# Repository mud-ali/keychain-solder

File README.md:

# keychain-solder

part of https://solder.hackclub.com/

## Description

This project is just a simple keychain with a few LEDs and a motor that turns on with the press of a button

## Bill of Materials

- Battery Holder x1
- 220 $\Omega$ Resistor x1
- Push Button x1
- LED x5
- Vibration Motor x1

## Screenshots 

### verification info

Slack name: `Mudasir`

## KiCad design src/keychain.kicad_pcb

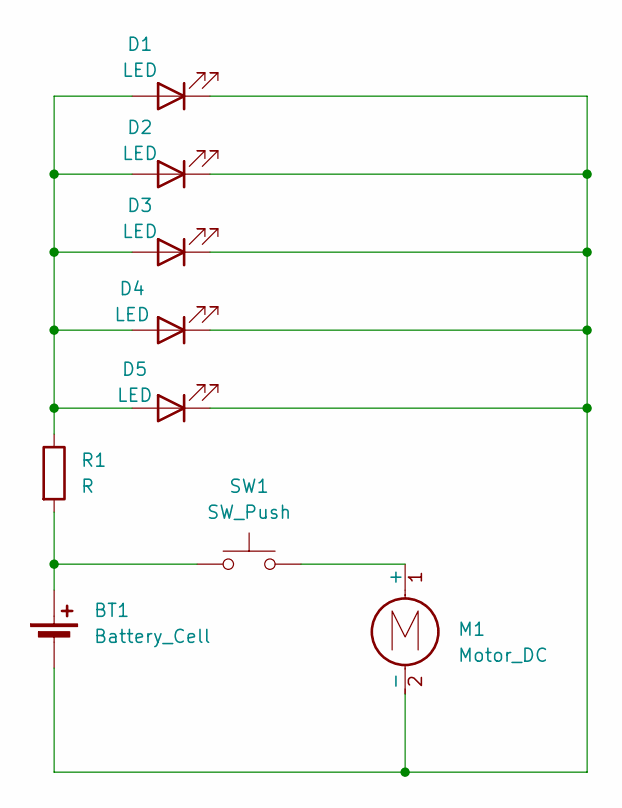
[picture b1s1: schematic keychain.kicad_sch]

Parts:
BT1: Battery_Cell; BatteryHolder_Keystone_3034_1x20mm
D1, D2, D3, D4, D5: LED; LED_D5.0mm
M1: Motor_DC; PinHeader_1x02_P2.54mm_Vertical
R1: R; R_Axial_DIN0207_L6.3mm_D2.5mm_P7.62mm_Horizontal
SW1: SW_Push; SW_PUSH_6mm

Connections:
unnamed: BT1.1 (+), R1.2, SW1.1
unnamed: BT1.2 (-), D1.1 (K), D2.1 (K), D3.1 (K), D4.1 (K), D5.1 (K), M1.2 (-)
unnamed: D1.2 (A), D2.2 (A), D3.2 (A), D4.2 (A), D5.2 (A), R1.1
unnamed: M1.1 (+), SW1.2

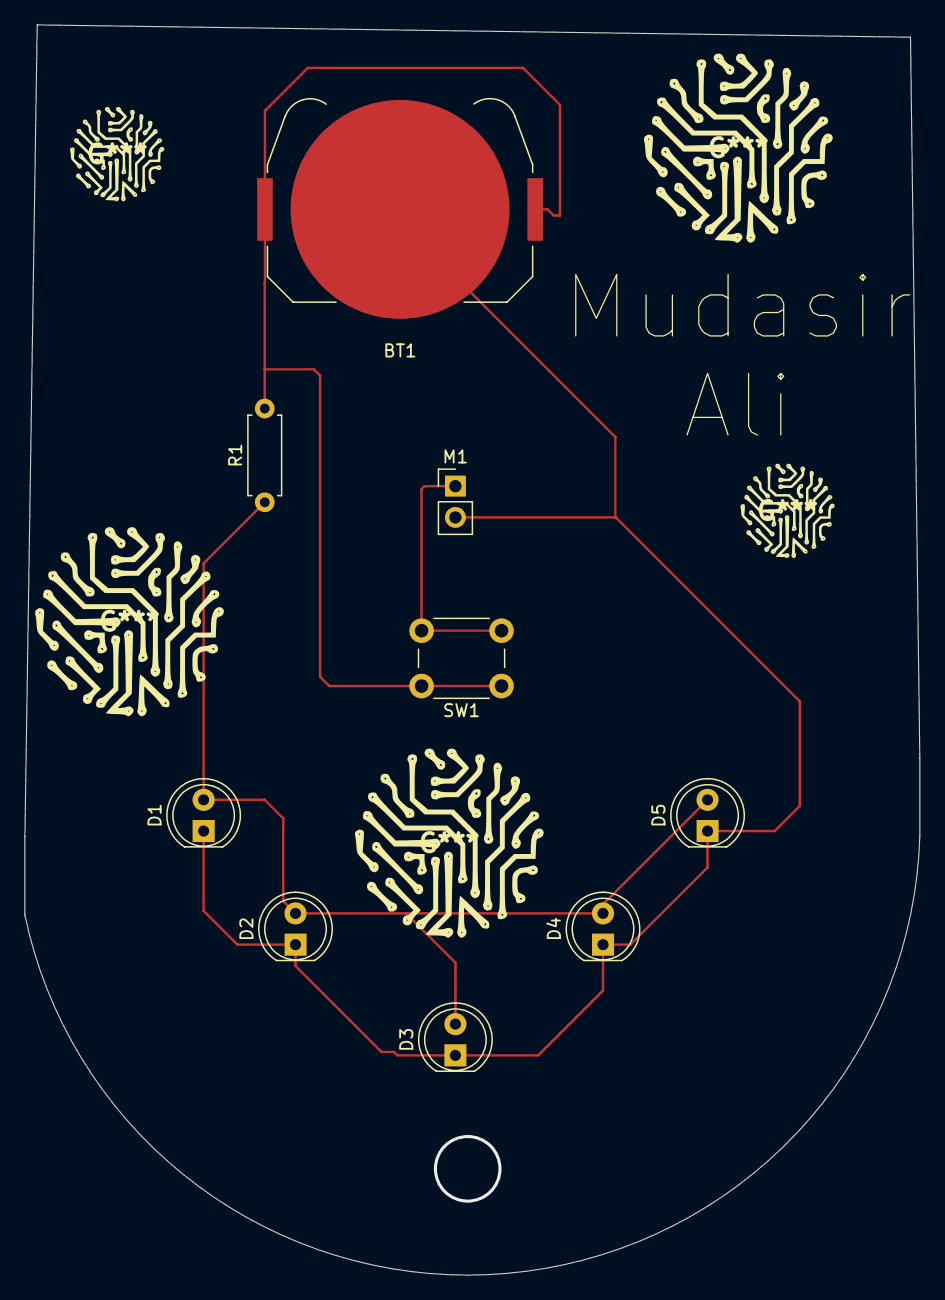
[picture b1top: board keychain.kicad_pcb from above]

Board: 2 copper layers, 72.8 x 101.6 mm, 9 parts (0 on the bottom side), 4 nets.

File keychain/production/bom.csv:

Designator,Footprint,Quantity,Value,LCSC Part #
BT1,BatteryHolder_Keystone_3034_1x20mm,1,Battery_Cell,
"D1, D2, D3, D4, D5",LED_D5.0mm,5,LED,
M1,PinHeader_1x02_P2.54mm_Vertical,1,Motor_DC,
R1,R_Axial_DIN0207_L6.3mm_D2.5mm_P7.62mm_Horizontal,1,R,
SW1,SW_PUSH_6mm,1,SW_Push,

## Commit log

2025-06-18 add project files
2025-06-18 rename source directory
2025-06-18 autosave deleted
2025-07-01 add some silkscreen art
2025-07-01 update screenshots
